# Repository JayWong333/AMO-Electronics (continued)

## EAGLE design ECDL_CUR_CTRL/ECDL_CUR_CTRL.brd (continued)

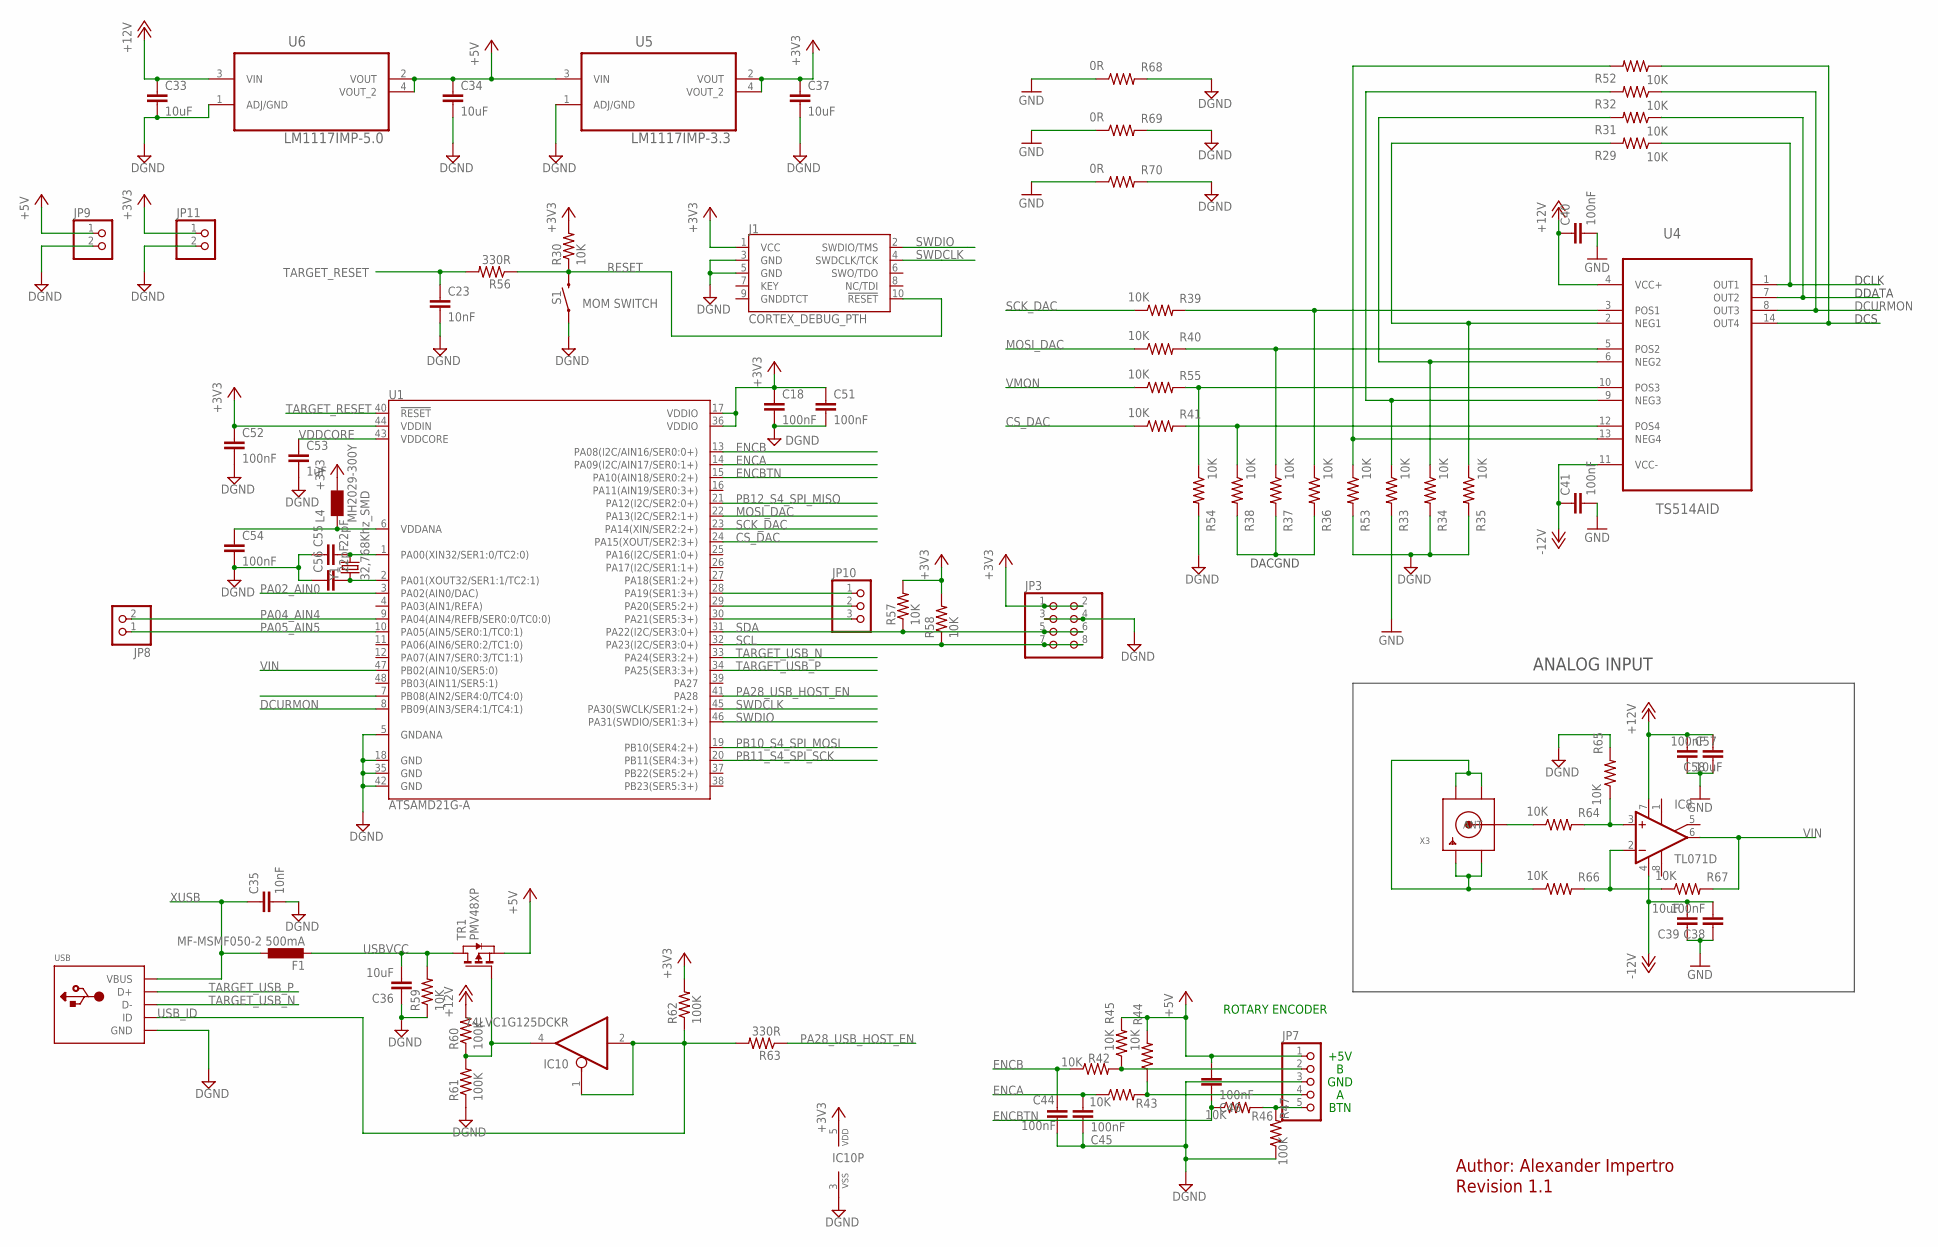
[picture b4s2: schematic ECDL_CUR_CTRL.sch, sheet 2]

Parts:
C18, C38, C40, C41, C44, C45, C46, C51, C52, C54, C58: 100nF; C0805
C23, C35: 10nF; C0805
C33, C34, C36, C37, C39, C57: 10uF; C0805
C53: 1uF; C0805
C55, C56: 22pF; C0805
F1: MF-MSMF050-2 500mA; PROTEZIONE_L1812
IC8: TL071D; SO08
IC10: 74LVC1G125DCKR; INTEGRATEDCIRCUITS_SC70-5
J1: CORTEX_DEBUG_PTH; 2X5-PTH-1.27MM
JP3: PINHD-2X4; 2X04
JP7: PINHD-1X5; 1X05
JP8, JP9, JP11: PINHD-1X2; 1X02
JP10: PINHD-1X3; 1X03
L4: MH2029-300Y; PROTEZIONE_0805
R29, R30, R31, R32, R33, R34, R35, R36, R37, R38, R39, R40, R41, R42, R43, R44, R45, R46, R52, R53, R54, R55, R57, R58, R59, R64, R65, R66, R67: 10K; R0805
R47, R60, R61, R62: 100K; R0805
R56, R63: 330R; R0805
R68, R69, R70: 0R; R0805
S1: MOM SWITCH; TACTILE_SWITCH_SMD_5.2MM
TR1: PMV48XP; TRANSISTORS_SOT-23
U1: ATSAMD21G-A; TQFP-48
U4: TS514AID; SOIC127P600X175-14N
U5: LM1117IMP-3.3; SOT230P696X180-4N
U6: LM1117IMP-5.0; SOT230P696X180-4N
USB: USBMINIB; USB-MINIB
X3: SMACONNECTOR; SMA90_DIP
Y1: 32,768Khz_SMD; CRISTALLI_RESONATOR_EPSON_FC_145

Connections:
+3V3: C18.1, C37.1, C51.1, C52.1, IC10.5 (VDD), J1.1 (VCC), JP3.1, JP3.2, JP11.1, L4.2, R30.2, R57.2, R58.2, R62.2, U1.17 (VDDIO), U1.36 (VDDIO), U1.44 (VDDIN), U5.2 (VOUT), U5.4 (VOUT_2)
+5V: C34.1, C46.1, JP7.1, JP9.1, R44.2, R45.2, TR1.2 (S), U5.3 (VIN), U6.2 (VOUT), U6.4 (VOUT_2)
+12V: C33.1, C40.1, C57.1, C58.2, IC8.7 (V+), R60.2, U4.4 (VCC+), U6.3 (VIN); also elsewhere on the board
-12V: C38.2, C39.2, C41.1, IC8.4 (V-), U4.11 (VCC-); also elsewhere on the board
CS_DAC: R41.1, U1.24 (PA15(XOUT/SER2:3+))
DACGND: R36.2, R37.2, R38.2; also elsewhere on the board
DCLK: R29.1, U4.1 (OUT1); also elsewhere on the board
DCS: R52.1, U4.14 (OUT4); also elsewhere on the board
DCURMON: R32.1, U1.8 (PB09(AIN3/SER4:1/TC4:1)), U4.8 (OUT3)
DDATA: R31.1, U4.7 (OUT2); also elsewhere on the board
DGND: C18.2, C23.2, C33.2, C34.2, C35.2, C36.1, C37.2, C44.2, C45.2, C51.2, C52.2, C53.2, C54.2, C55.1, C56.1, IC10.3 (VSS), J1.3 (GND), J1.5 (GND), JP3.3, JP3.4, JP7.3, JP9.2, JP11.2, R34.2, R35.2, R47.1, R53.2, R54.2, R59.1, R61.1, R65.2, R68.2, R69.2, R70.2, S1.1, U1.5 (GNDANA), U1.18 (GND), U1.35 (GND), U1.42 (GND), U5.1 (ADJ/GND), U6.1 (ADJ/GND), USB.GND
ENCA: C45.1, R43.1, U1.14 (PA09(I2C/AIN17/SER0:1+))
ENCB: C44.1, R42.1, U1.13 (PA08(I2C/AIN16/SER0:0+))
ENCBTN: C46.2, R46.1, U1.15 (PA10(AIN18/SER0:2+))
GND: C38.1, C39.1, C40.2, C41.2, C57.2, C58.1, R33.2, R68.1, R69.1, R70.1; also elsewhere on the board
MOSI_DAC: R40.1, U1.22 (PA13(I2C/SER2:1+))
unnamed: R29.2, R35.1, U4.2 (NEG1)
unnamed: R36.1, R39.2, U4.3 (POS1)
unnamed: C54.1, L4.1, U1.6 (VDDANA)
unnamed: R31.2, R34.1, U4.6 (NEG2)
unnamed: R66.1, X3.GND1, X3.GND2, X3.GND3, X3.GND4
unnamed: R64.1, X3.ANTENNA (ANT)
unnamed: JP7.2, R42.2, R45.1
unnamed: IC8.3 (+IN), R64.2, R65.1
unnamed: R32.2, R33.1, U4.9 (NEG3)
unnamed: JP7.4, R43.2, R44.1
unnamed: R37.1, R40.2, U4.5 (POS2)
unnamed: R38.1, R41.2, U4.12 (POS4)
unnamed: JP7.5, R46.2, R47.2
unnamed: C55.2, U1.1 (PA00(XIN32/SER1:0/TC2:0)), Y1.P$2 (2)
unnamed: C56.2, U1.2 (PA01(XOUT32/SER1:1/TC2:1)), Y1.P$1 (1)
unnamed: IC10.4 (O), R60.1, R61.2, TR1.3 (G)
unnamed: IC8.2 (-IN), R66.2, R67.1
unnamed: JP10.3, U1.30 (PA21(SER5:3+))
unnamed: JP10.2, U1.29 (PA20(SER5:2+))
unnamed: JP10.1, U1.28 (PA19(SER1:3+))
unnamed: R54.1, R55.2, U4.10 (POS3)
unnamed: R52.2, R53.1, U4.13 (NEG4)
PA02_AIN0: U1.3 (PA02(AIN0/DAC))
PA04_AIN4: JP8.2, U1.9 (PA04(AIN4/REFB/SER0:0/TC0:0))
PA05_AIN5: JP8.1, U1.10 (PA05(AIN5/SER0:1/TC0:1))
PA28_USB_HOST_EN: R63.1, U1.41 (PA28)
PB10_S4_SPI_MOSI: U1.19 (PB10(SER4:2+))
PB11_S4_SPI_SCK: U1.20 (PB11(SER4:3+))
PB12_S4_SPI_MISO: U1.21 (PA12(I2C/SER2:0+))
RESET: J1.10 (!RESET), R30.1, R56.1, S1.3 (2)
SCK_DAC: R39.1, U1.23 (PA14(XIN/SER2:2+))
SCL: JP3.7, JP3.8, R58.1, U1.32 (PA23(I2C/SER3:0+))
SDA: JP3.5, JP3.6, R57.1, U1.31 (PA22(I2C/SER3:0+))
SWDCLK: J1.4 (SWDCLK/TCK), U1.45 (PA30(SWCLK/SER1:2+))
SWDIO: J1.2 (SWDIO/TMS), U1.46 (PA31(SWDIO/SER1:3+))
TARGET_RESET: C23.1, R56.2, U1.40 (!RESET!)
TARGET_USB_N: U1.33 (PA24(SER3:2+)), USB.D-
TARGET_USB_P: U1.34 (PA25(SER3:3+)), USB.D+
USBVCC: C36.2, F1.2, R59.2, TR1.1 (D)
USB_ID: IC10.1 (OE), IC10.2 (I), R62.1, R63.2, USB.ID
VDDCORE: C53.1, U1.43 (VDDCORE)
VIN: IC8.6 (OUT), R67.2, U1.47 (PB02(AIN10/SER5:0))
VMON: R55.1; also elsewhere on the board
XUSB: C35.1, F1.1, USB.VBUS

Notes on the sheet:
DCLK
DACGND
DDATA
DCS
ROTARY ENCODER
+5V
BTN
GND
DCURMON
Author: Alexander Impertro
Revision 1.1
ANALOG INPUT

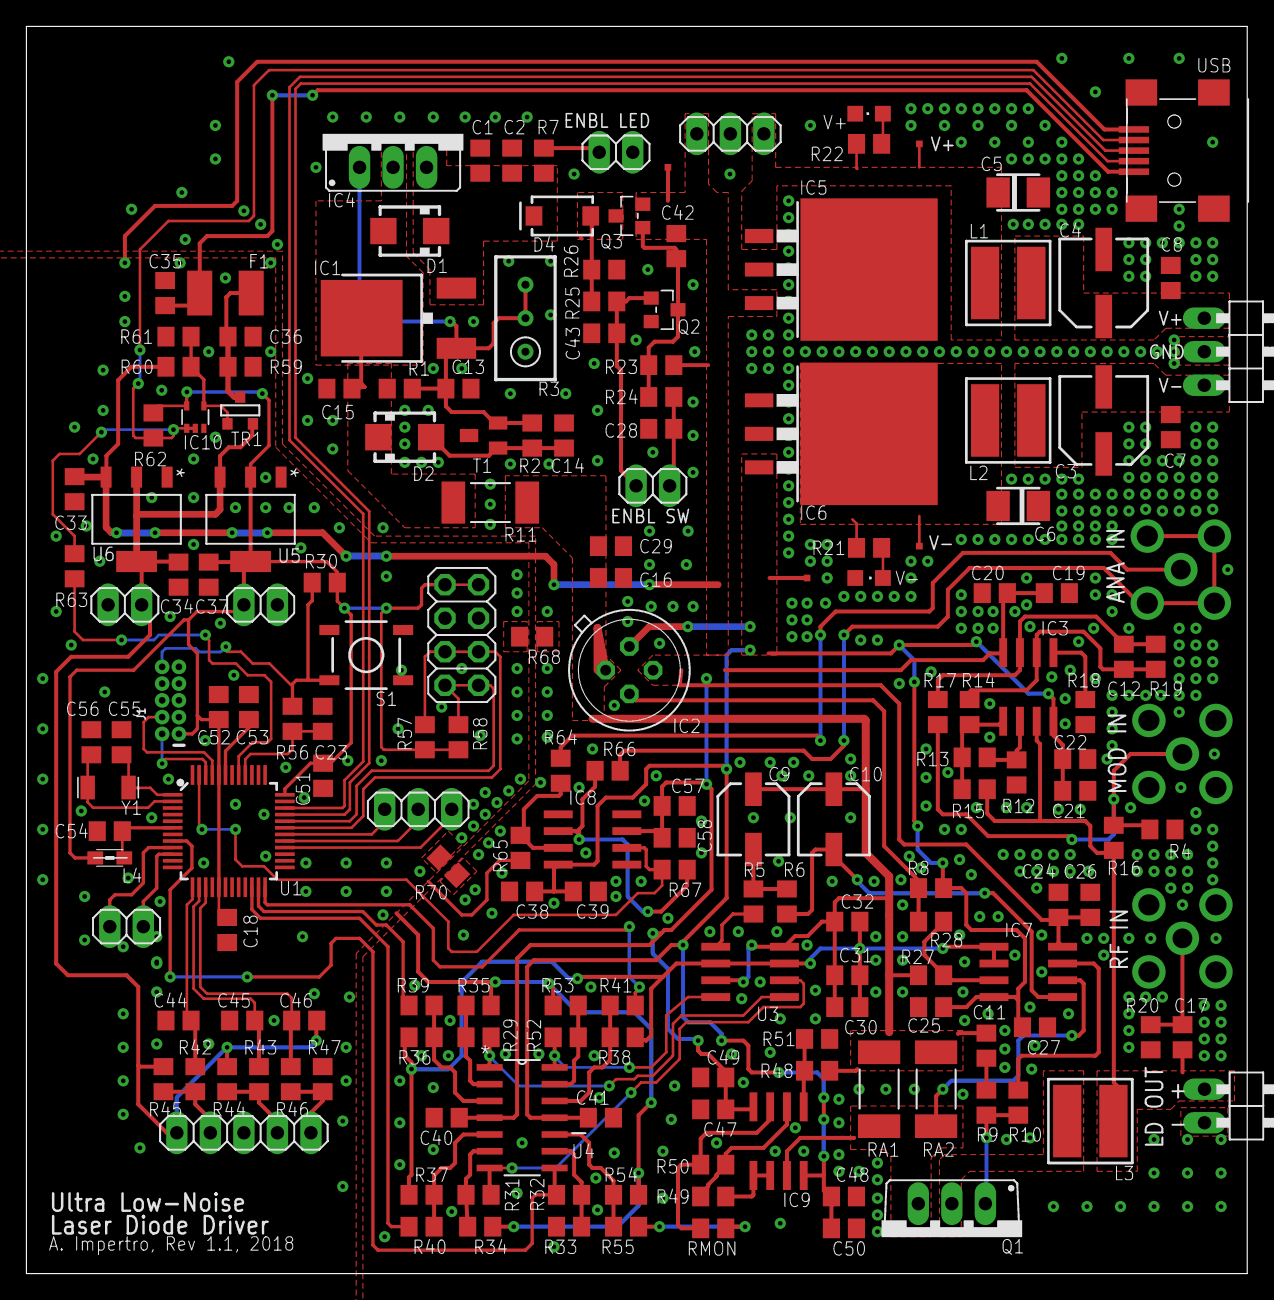
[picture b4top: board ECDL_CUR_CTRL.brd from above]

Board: 2 copper layers, 92.5 x 94.5 mm, 183 parts (1 on the bottom side), 94 nets.

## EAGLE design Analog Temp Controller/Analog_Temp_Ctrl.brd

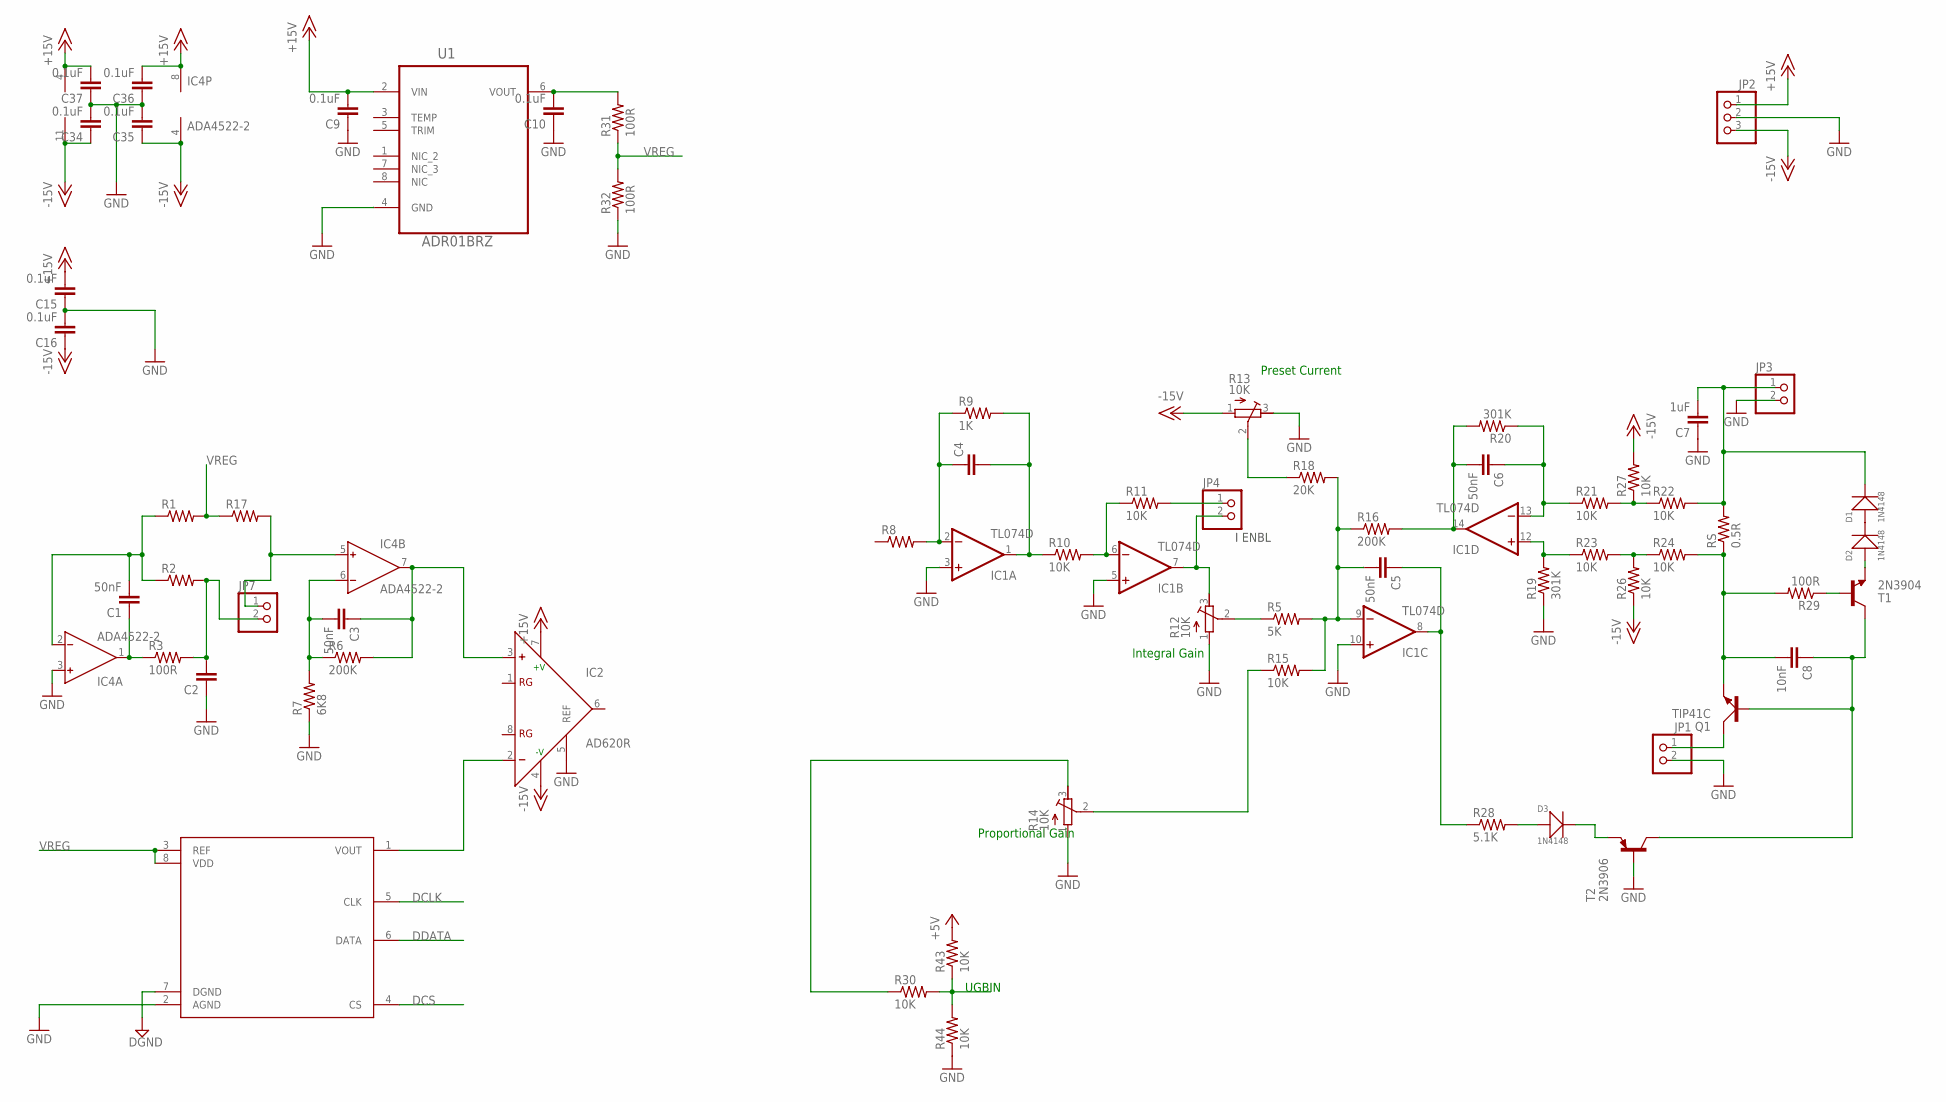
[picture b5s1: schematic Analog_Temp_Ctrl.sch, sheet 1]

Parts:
C1, C3, C5, C6: 50nF; C0805
C2, C4: C-EUC0805; C0805
C7: 1uF; C0805
C8: 10nF; C0805
C9, C10, C15, C16, C34, C35, C36, C37: 0.1uF; C0805
D1, D2, D3: 1N4148; LL-34
IC1: TL074D; SO14
IC2: AD620R; SO8
IC4: ADA4522-2; SO8
JP1, JP3: PINHD-1X2/90; 1X02/90
JP2: PINHD-1X3/90; 1X03/90
JP4, JP7: PINHD-1X2; 1X02
Q1: TIP41C; TO220AV
R1, R2, R8, R17: R-US_R0805; R0805
R3, R29, R31, R32: 100R; R0805
R5: 5K; R0805
R6, R16: 200K; R0805
R7: 6K8; R0805
R9: 1K; R0805
R10, R11, R15, R21, R22, R23, R24, R26, R27, R30, R43, R44: 10K; R0805
R12, R13, R14: 10K; RTRIM3296W
R18: 20K; R0805
R19, R20: 301K; R0805
R28: 5.1K; R0805
RS: 0.5R; R2512
T1: 2N3904; SOT23-BEC
T2: 2N3906; SOT23-BEC
U1: ADR01BRZ; SOIC127P600X175-8N
U3: AD5541; SOIC-8

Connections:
+5V: R43.2; also elsewhere on the board
+15V: C9.2, C15.2, C36.2, C37.2, IC1.4 (V+), IC2.7 (+V), IC4.8 (V+), JP2.1, U1.2 (VIN); also elsewhere on the board
-15V: C16.1, C34.1, C35.1, IC1.11 (V-), IC2.4 (-V), IC4.4 (V-), JP2.3, R13.1 (A), R26.1, R27.2
DCLK: U3.5 (CLK); also elsewhere on the board
DCS: U3.4 (CS); also elsewhere on the board
DDATA: U3.6 (DATA); also elsewhere on the board
DGND: U3.7 (DGND); also elsewhere on the board
GND: C2.1, C7.1, C9.1, C10.1, C15.1, C16.2, C34.2, C35.2, C36.1, C37.1, IC1.3 (+IN), IC1.5 (+IN), IC1.10 (+IN), IC2.5 (REF), IC4.3 (IN+), JP1.2, JP2.2, JP3.2, R7.1, R12.1 (A), R13.3 (E), R14.1 (A), R19.1, R32.1, R44.1, T2.B, U1.4 (GND), U3.2 (AGND); also elsewhere on the board
unnamed: C1.2, IC4.2 (IN-), R1.1, R2.1
unnamed: JP4.1, R11.2
unnamed: R5.1, R12.2 (S)
unnamed: C1.1, IC4.1 (OUT), R3.1
unnamed: C4.1, IC1.2 (-IN), R8.2, R9.1
unnamed: C2.2, JP7.2, R2.2, R3.2
unnamed: C3.1, IC2.3 (+), IC4.7 (OUT), R6.2
unnamed: R14.2 (S), R15.1
unnamed: C3.2, IC4.6 (IN-), R6.1, R7.2
unnamed: R14.3 (E), R30.1
unnamed: C6.2, IC1.14 (OUT), R16.2, R20.2
unnamed: R13.2 (S), R18.1
unnamed: C5.2, IC1.9 (-IN), R5.2, R15.2, R16.1, R18.2
unnamed: C4.2, IC1.1 (OUT), R9.2, R10.1
unnamed: C5.1, IC1.8 (OUT), R28.1
unnamed: IC1.12 (+IN), R19.2, R23.1
unnamed: R21.2, R22.1, R27.1
unnamed: C6.1, IC1.13 (-IN), R20.1, R21.1
unnamed: IC1.7 (OUT), JP4.2, R12.3 (E)
unnamed: R23.2, R24.1, R26.2
unnamed: C7.2, D1.C (-), JP3.1, R22.2, RS.2
unnamed: C8.2, Q1.E, R24.2, R29.2, RS.1
unnamed: C10.2, R31.2, U1.6 (VOUT)
unnamed: D1.A (+), D2.C (-)
unnamed: D3.A (+), R28.2
unnamed: D3.C (-), T2.E
unnamed: D2.A (+), T1.E
unnamed: R29.1, T1.B
unnamed: C8.1, Q1.B, T1.C, T2.C
unnamed: JP1.1, Q1.C
unnamed: IC1.6 (-IN), R10.2, R11.1
unnamed: IC2.2 (-), U3.1 (VOUT)
RW: IC4.5 (IN+), JP7.1, R17.2
UGBIN: R30.2, R43.1, R44.2; also elsewhere on the board
VREG: R1.2, R17.1, R31.1, R32.2, U3.3 (REF), U3.8 (VDD)

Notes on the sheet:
Integral Gain
Preset Current
Proportional Gain
UGBIN
I ENBL

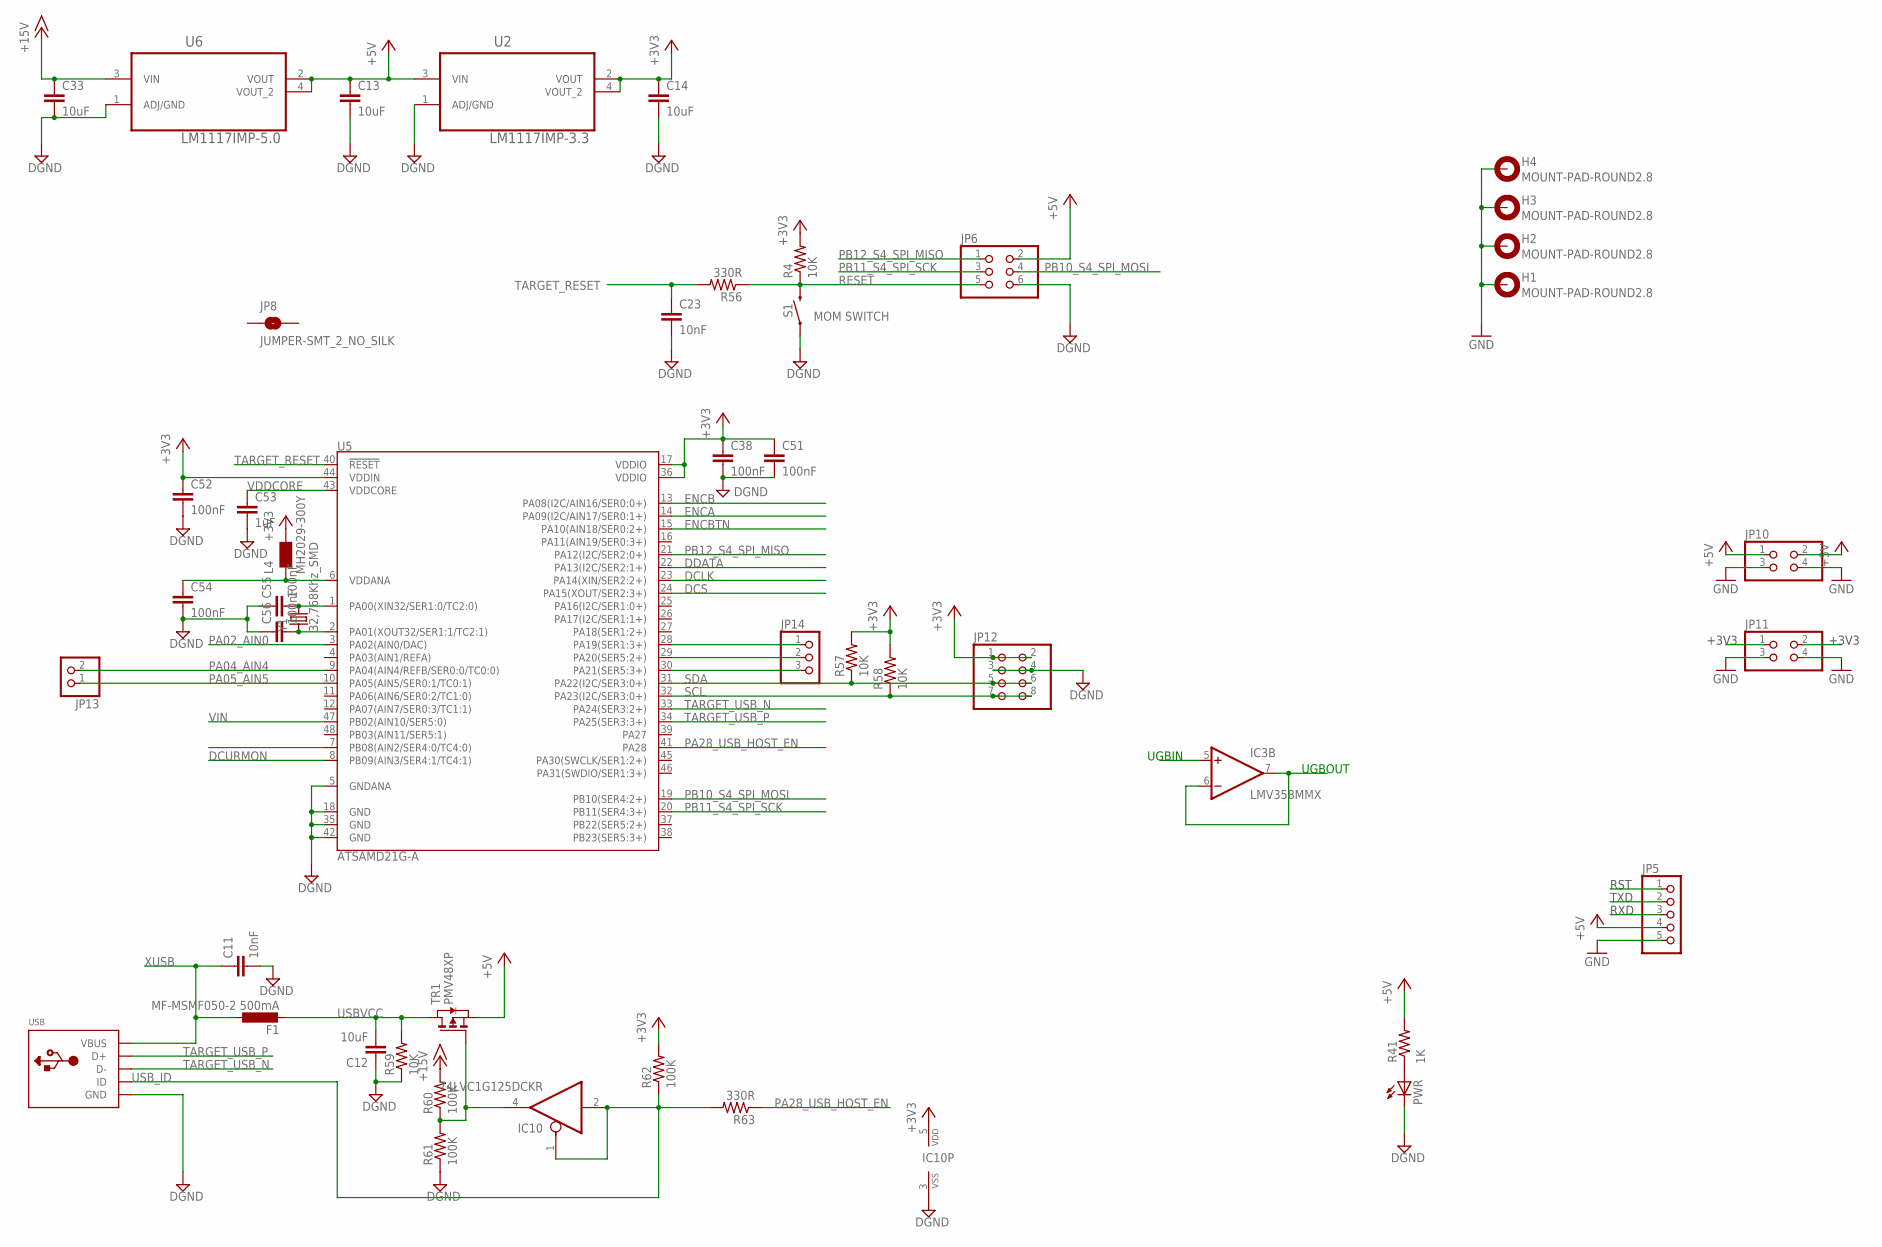
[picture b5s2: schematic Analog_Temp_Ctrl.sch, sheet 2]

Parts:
C11, C23: 10nF; C0805
C12, C13, C14, C33: 10uF; C0805
C38, C51, C52, C54, C55, C56: 100nF; C0805
C53: 1uF; C0805
F1: MF-MSMF050-2 500mA; PROTEZIONE_L1812
H1, H2, H3, H4: MOUNT-PAD-ROUND2.8; 2,8-PAD
IC3: LMV358MMX; MSOP08
IC10: 74LVC1G125DCKR; INTEGRATEDCIRCUITS_SC70-5
JP5: PINHD-1X5; 1X05
JP6: PINHD-2X3; 2X03
JP8: JUMPER-SMT_2_NO_SILK; SMT-JUMPER_2_NO_SILK
JP10, JP11: PINHD-2X2; 2X02
JP12: PINHD-2X4; 2X04
JP13: PINHD-1X2; 1X02
JP14: PINHD-1X3; 1X03
L4: MH2029-300Y; PROTEZIONE_0805
PWR: LEDCHIPLED_0805; CHIPLED_0805
R4, R57, R58, R59: 10K; R0805
R41: 1K; R0805
R56, R63: 330R; R0805
R60, R61, R62: 100K; R0805
S1: MOM SWITCH; TACTILE_SWITCH_SMD_5.2MM
TR1: PMV48XP; TRANSISTORS_SOT-23
U2: LM1117IMP-3.3; SOT230P696X180-4N
U5: ATSAMD21G-A; TQFP-48
U6: LM1117IMP-5.0; SOT230P696X180-4N
USB: USBMINIB; USB-MINIB
Y1: 32,768Khz_SMD; CRISTALLI_RESONATOR_EPSON_FC_145

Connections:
3V3: JP11.1, JP11.2
+3V3: C14.1, C38.1, C51.1, C52.1, IC10.5 (VDD), JP12.1, JP12.2, L4.2, R4.2, R57.2, R58.2, R62.2, U2.2 (VOUT), U2.4 (VOUT_2), U5.17 (VDDIO), U5.36 (VDDIO), U5.44 (VDDIN)
+5V: C13.1, JP5.4, JP6.2, JP10.1, JP10.2, R41.2, TR1.2 (S), U2.3 (VIN), U6.2 (VOUT), U6.4 (VOUT_2); also elsewhere on the board
+15V: C33.1, R60.2, U6.3 (VIN); also elsewhere on the board
DCLK: U5.23 (PA14(XIN/SER2:2+)); also elsewhere on the board
DCS: U5.24 (PA15(XOUT/SER2:3+)); also elsewhere on the board
DCURMON: U5.8 (PB09(AIN3/SER4:1/TC4:1))
DDATA: U5.22 (PA13(I2C/SER2:1+)); also elsewhere on the board
DGND: C11.2, C12.1, C13.2, C14.2, C23.2, C33.2, C38.2, C51.2, C52.2, C53.2, C54.2, C55.1, C56.1, IC10.3 (VSS), JP6.6, JP12.3, JP12.4, PWR.C, R59.1, R61.1, S1.1, U2.1 (ADJ/GND), U5.5 (GNDANA), U5.18 (GND), U5.35 (GND), U5.42 (GND), U6.1 (ADJ/GND), USB.GND; also elsewhere on the board
ENCA: U5.14 (PA09(I2C/AIN17/SER0:1+))
ENCB: U5.13 (PA08(I2C/AIN16/SER0:0+))
ENCBTN: U5.15 (PA10(AIN18/SER0:2+))
GND: H1.B2,8, H2.B2,8, H3.B2,8, H4.B2,8, JP5.5, JP10.3, JP10.4, JP11.3, JP11.4; also elsewhere on the board
unnamed: C54.1, L4.1, U5.6 (VDDANA)
unnamed: IC10.4 (O), R60.1, R61.2, TR1.3 (G)
unnamed: PWR.A, R41.1
unnamed: C55.2, U5.1 (PA00(XIN32/SER1:0/TC2:0)), Y1.P$2 (2)
unnamed: C56.2, U5.2 (PA01(XOUT32/SER1:1/TC2:1)), Y1.P$1 (1)
unnamed: JP14.3, U5.30 (PA21(SER5:3+))
unnamed: JP14.2, U5.29 (PA20(SER5:2+))
unnamed: JP14.1, U5.28 (PA19(SER1:3+))
PA02_AIN0: U5.3 (PA02(AIN0/DAC))
PA04_AIN4: JP13.2, U5.9 (PA04(AIN4/REFB/SER0:0/TC0:0))
PA05_AIN5: JP13.1, U5.10 (PA05(AIN5/SER0:1/TC0:1))
PA28_USB_HOST_EN: R63.1, U5.41 (PA28)
PB10_S4_SPI_MOSI: JP6.4, U5.19 (PB10(SER4:2+))
PB11_S4_SPI_SCK: JP6.3, U5.20 (PB11(SER4:3+))
PB12_S4_SPI_MISO: JP6.1, U5.21 (PA12(I2C/SER2:0+))
RESET: JP6.5, R4.1, R56.1, S1.3 (2)
RST: JP5.1
RXD: JP5.3
SCL: JP12.7, JP12.8, R58.1, U5.32 (PA23(I2C/SER3:0+))
SDA: JP12.5, JP12.6, R57.1, U5.31 (PA22(I2C/SER3:0+))
TARGET_RESET: C23.1, R56.2, U5.40 (!RESET!)
TARGET_USB_N: U5.33 (PA24(SER3:2+)), USB.D-
TARGET_USB_P: U5.34 (PA25(SER3:3+)), USB.D+
TXD: JP5.2
UGBIN: IC3.5 (+IN); also elsewhere on the board
UGBOUT: IC3.6 (-IN), IC3.7 (OUT)
USBVCC: C12.2, F1.2, R59.2, TR1.1 (D)
USB_ID: IC10.1 (OE), IC10.2 (I), R62.1, R63.2, USB.ID
V+: IC3.8 (V+)
V-: IC3.4 (V-)
VDDCORE: C53.1, U5.43 (VDDCORE)
VIN: U5.47 (PB02(AIN10/SER5:0))
XUSB: C11.1, F1.1, USB.VBUS

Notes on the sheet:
RST
TXD
RXD
+3V3
UGBIN
UGBOUT

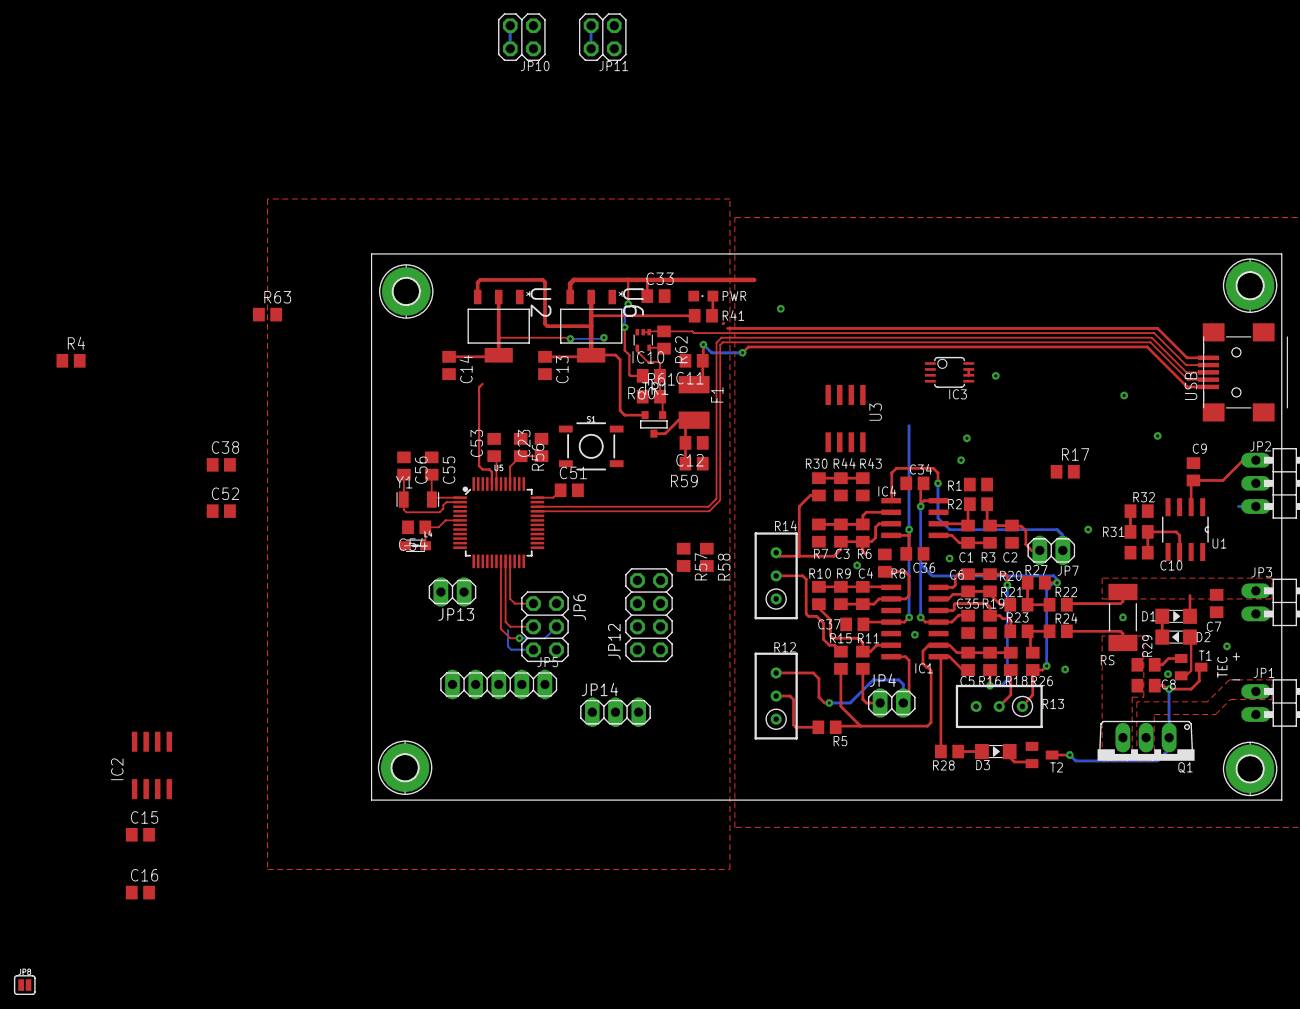
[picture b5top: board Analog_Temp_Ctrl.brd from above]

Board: 2 copper layers, 100.0 x 60.0 mm, 112 parts (0 on the bottom side), 70 nets.

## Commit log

2017-12-03 Moved project files to GitHub. Revision 1.0.
    As manufactured in the first iteration.
2017-12-03 Added analog temperature controller.
2017-12-06 Completed Temperature Controller, Rdy for Mfg.
2018-01-04 Preliminary changes to new version.
    New features: Microntroller for current driver as well, seperate A/D
    grounding, upgrade to ARM Cortec uC, several other improvements.
2018-01-08 Rev1.1 of CUR CTRL Complete, Ready for Mfg. Temp Ctrl WIP
2018-01-27 Added a Controller for the Pfeiffer IKR/PKR Series Compact Gauges. Temp Ctrl WIP...
2018-02-17 Added Pfeiffer G.auge Controller Schematics + FW
2018-03-27 Changes to Analog PID. Added LTC1923 Design.
